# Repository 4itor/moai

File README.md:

# moai Keyboard

A small, 34 key, low(ish) profile keyboard with MX switches.

The keyboard is caseless, using just the plate and the pcb, with a maple woodcut (3.3mm height) between both. No screws, the soldered switches keep everything in place.

The wood gives enough stability and it's quite sturdy compared to other caseless builds I've done before (even the ones that used screws).

The texture on top of the plate is created poking holes on the `Cu` layer below; tried just this once and results where better than expected; As the plate is simmetrical I created two designs (one on each side), but only used the textured one for now.

> **Word of advice** : The distance between each pair of thumb keys is tenths of a millimeter less than the standard for 1.25U keys, this is intentional. I have found no incompatibilities in any keycap profiles thrown at it (Cherry, MDA/XVX, XDA, SDA, MT3, etc) from several vendors, but your milleage may vary.

See more pictures in the [Gallery](gallery/README.md).

## About moai

The moai logo is an [ambigram](https://en.wikipedia.org/wiki/Ambigram) on the romanized japanese term `moai`.

Moais (模合, Mo-ai) are social support groups that form in order to provide varying support from social, financial, health, or spiritual interests.

Moai means "meeting for a common purpose" in Japanese and originated from the social support groups in Okinawa, Japan.

Source: [Wikipedia](https://en.wikipedia.org/wiki/Moai_(social_support_groups))

## Design

It was designed using Ergogen and Kicad.

Original procedural design on [Ergogen](ergogen/moai.yaml) folder and Kicad+Gerbers on [Build Files](build_files/)

## Build

See [build notes](BUILD.md)

## Other Channels

* [Discord](https://discord.com/channels/714176584269168732/1127694421861871636)

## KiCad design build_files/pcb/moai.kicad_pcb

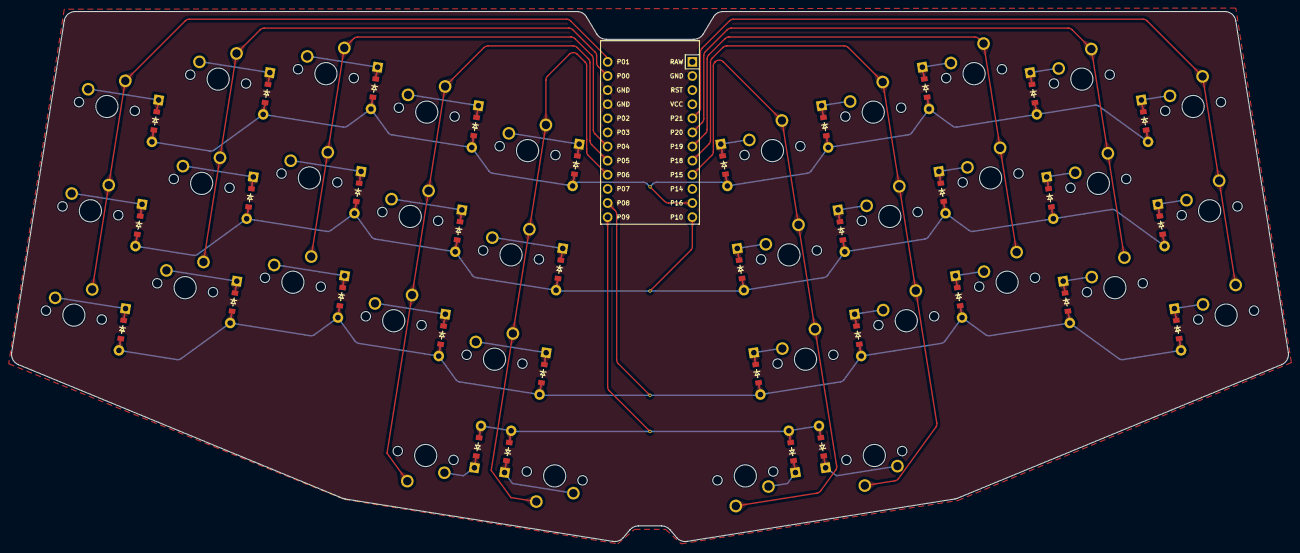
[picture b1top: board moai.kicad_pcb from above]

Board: 2 copper layers, 229.8 x 95.4 mm, 69 parts (0 on the bottom side), 49 nets.

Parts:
10.001251, 10.001252, 10.001253, 10.001254, 10.001255, 10.001256, 10.001257, 10.001258, 10.001259, 10.0012510, 10.0012511, 10.0012512, 10.0012513, 10.0012514, 10.0012515, 10.0012516, 10.0012517, 10.0012518, 10.0012519, 10.0012520, 10.0012521, 10.0012522, 10.0012523, 10.0012524, 10.0012525, 10.0012526, 10.0012527, 10.0012528, 10.0012529, 10.0012530, 10.0012531, 10.0012532, 10.0012533, 10.0012534: MX
D1, D2, D3, D4, D5, D6, D7, D8, D9, D10, D11, D12, D13, D14, D15, D16, D17, D18, D19, D20, D21, D22, D23, D24, D25, D26, D27, D28, D29, D30, D31, D32, D33, D34: ComboDiode
MCU1: ProMicro

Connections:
GND: MCU1.2, MCU1.15, MCU1.16
P0: 10.001254.1, 10.001255.1, 10.001256.1, MCU1.14
P1: 10.001251.1, 10.001252.1, 10.001253.1, MCU1.13
P4: 10.001257.1, 10.001258.1, 10.001259.1, MCU1.19
P5: 10.0012510.1, 10.0012511.1, 10.0012512.1, 10.0012531.1, MCU1.20
P6: 10.0012513.1, 10.0012514.1, 10.0012515.1, 10.0012532.1, MCU1.21
P8: D1.2, D4.2, D7.2, D10.2, D13.2, D16.2, D19.2, D22.2, D25.2, D28.2, MCU1.23
P9: D31.2, D32.2, D33.2, D34.2, MCU1.24
P10: D2.2, D5.2, D8.2, D11.2, D14.2, D17.2, D20.2, D23.2, D26.2, D29.2, MCU1.12
P15: 10.0012528.1, 10.0012529.1, 10.0012530.1, 10.0012534.1, MCU1.9
P16: D3.2, D6.2, D9.2, D12.2, D15.2, D18.2, D21.2, D24.2, D27.2, D30.2, MCU1.11
P18: 10.0012525.1, 10.0012526.1, 10.0012527.1, 10.0012533.1, MCU1.8
P19: 10.0012522.1, 10.0012523.1, 10.0012524.1, MCU1.7
P20: 10.0012519.1, 10.0012520.1, 10.0012521.1, MCU1.6
P21: 10.0012516.1, 10.0012517.1, 10.0012518.1, MCU1.5
index_bottom: 10.0012510.2, D10.1
index_home: 10.0012511.2, D11.1
index_top: 10.0012512.2, D12.1
inner_bottom: 10.0012513.2, D13.1
inner_default: 10.0012532.2, D32.1
inner_home: 10.0012514.2, D14.1
inner_top: 10.0012515.2, D15.1
middle_bottom: 10.001257.2, D7.1
middle_home: 10.001258.2, D8.1
middle_top: 10.001259.2, D9.1
mirror_index_bottom: 10.0012525.2, D25.1
mirror_index_home: 10.0012526.2, D26.1
mirror_index_top: 10.0012527.2, D27.1
mirror_inner_bottom: 10.0012528.2, D28.1
mirror_inner_default: 10.0012534.2, D33.1
mirror_inner_home: 10.0012529.2, D29.1
mirror_inner_top: 10.0012530.2, D30.1
mirror_middle_bottom: 10.0012522.2, D22.1
mirror_middle_home: 10.0012523.2, D23.1
mirror_middle_top: 10.0012524.2, D24.1
mirror_outer_default: 10.0012533.2, D34.1
mirror_pinky_bottom: 10.0012516.2, D16.1
mirror_pinky_home: 10.0012517.2, D17.1
mirror_pinky_top: 10.0012518.2, D18.1
mirror_ring_bottom: 10.0012519.2, D19.1
mirror_ring_home: 10.0012520.2, D20.1
mirror_ring_top: 10.0012521.2, D21.1
outer_default: 10.0012531.2, D31.1
pinky_bottom: 10.001251.2, D1.1
pinky_home: 10.001252.2, D2.1
pinky_top: 10.001253.2, D3.1
ring_bottom: 10.001254.2, D4.1
ring_home: 10.001255.2, D5.1
ring_top: 10.001256.2, D6.1

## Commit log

2023-06-18 Init files
2023-07-03 Photos
2023-07-03 Readme
2023-07-07 Gallery updates
2023-07-07 Fix Readme
2023-07-07 Readmes
2023-07-07 Gallery
2023-07-07 Build Notes (preliminary)
2023-07-07 Documentation
2023-07-07 Build notes
2023-07-07 Build
2023-07-07 Upgrade Controller Picture
2023-07-07 Switch pin clipping example.
2023-07-08 Update build document
2023-07-08 Added some build notes (in progress)
2023-07-08 Build Notes (in progress)
2023-08-20 Readme.
2023-10-31 Gerber Files for Pcb/Plate manufacturing
2023-11-01 Plate Gerbers
2026-03-31 Moai choc
